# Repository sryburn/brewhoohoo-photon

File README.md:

A particle photon based HERMS brewery controller with 3D printed encousure.
WORK IN PROGRESS

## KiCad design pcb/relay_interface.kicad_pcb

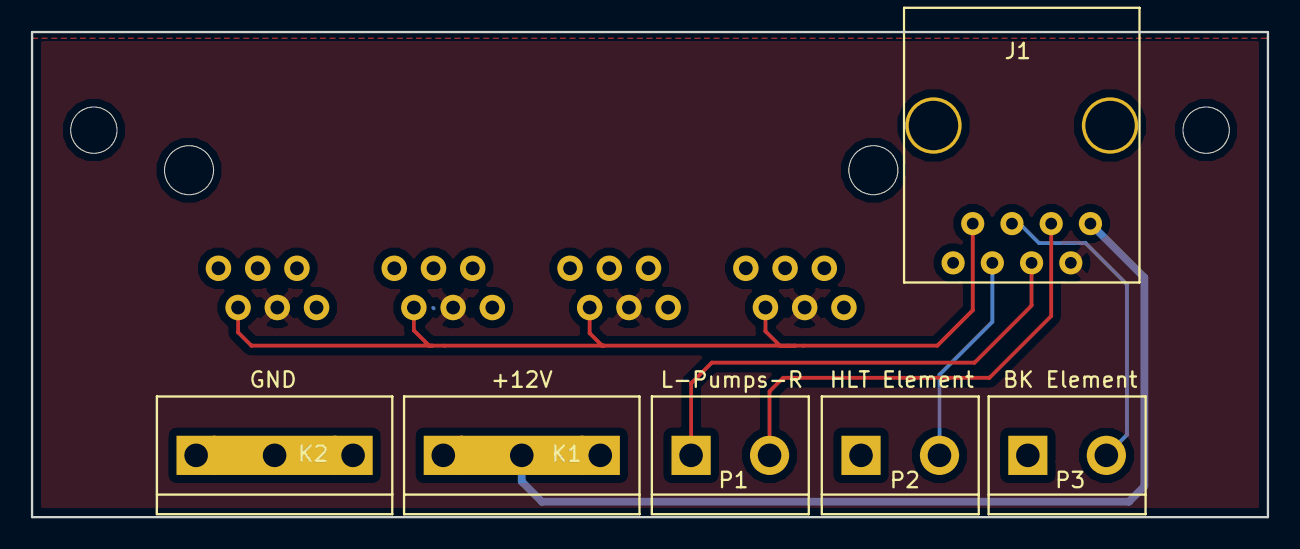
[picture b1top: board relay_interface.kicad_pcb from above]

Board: 2 copper layers, 80.0 x 31.4 mm, 7 parts (1 on the bottom side), 8 nets.

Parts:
J1: RJ45; RJ45_c-bmj-0102
J2: RJ12x4; CT660027-RJ12
K1, K2: CONN_3_V; bornier3
P1, P2, P3: CONN_2_V; bornier2

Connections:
+3V3: J1.2, J2.3, J2.9, J2.15, J2.21
+12V: J1.1, K1.1, K1.2, K1.3
/Element1: J1.6, P2.2
/Element2: J1.5, P3.2
/Pump1: J1.3, P1.2
/Pump2: J1.4, P1.1
/Temperature: J1.7, J2.5, J2.11, J2.17, J2.23
GND: J1.8, J2.4, J2.10, J2.16, J2.22, K2.1, K2.2, K2.3, P2.1, P3.1

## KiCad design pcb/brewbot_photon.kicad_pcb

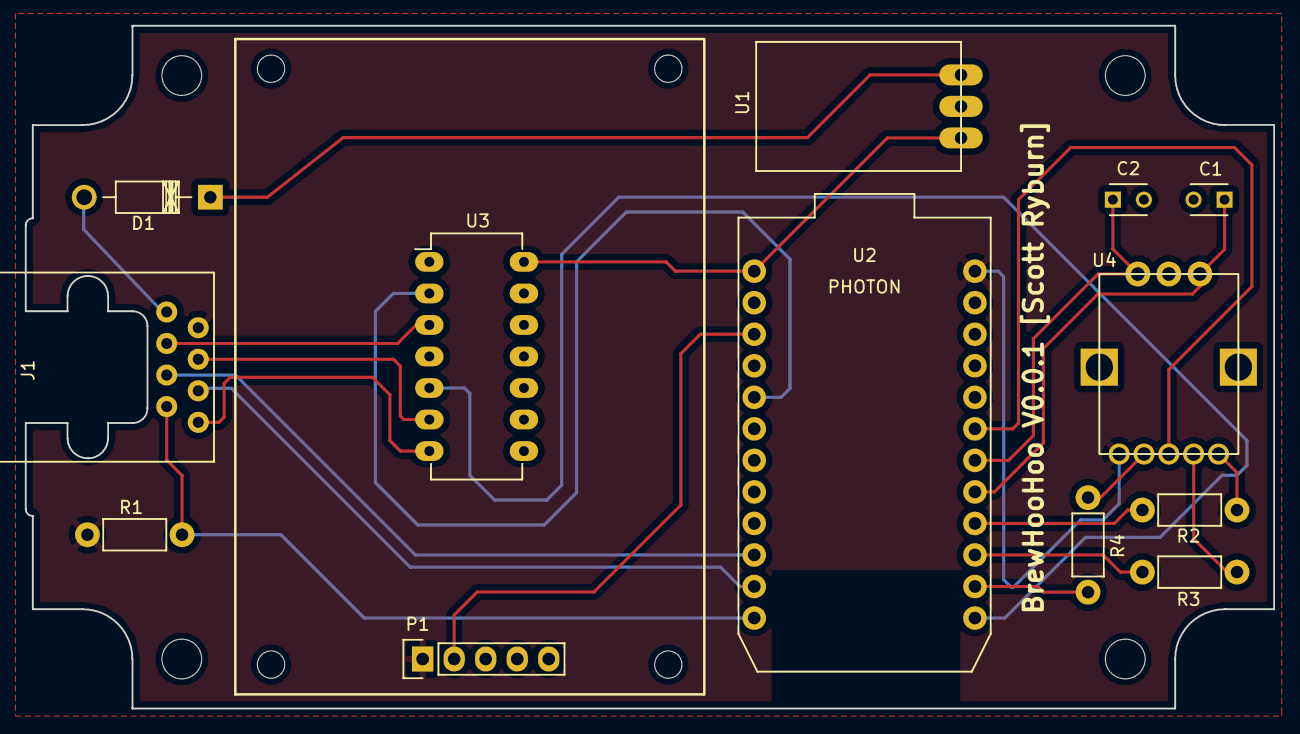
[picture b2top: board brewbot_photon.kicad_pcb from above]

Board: 2 copper layers, 100.6 x 55.0 mm, 17 parts (0 on the bottom side), 22 nets.

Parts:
C1, C2: 0.1uf; C_Disc_D3_P2.5
D1: 1N4007; Diode_DO-41_SOD81_Horizontal_RM10
J1: RJ45; RJ45_cA121601-ND_slim
P1: CONN_01X05; Pin_Header_Straight_1x05
R1: 4.7k; Resistor_Horizontal_RM7mm
R2: 56; Resistor_Horizontal_RM7mm
R3, R4: 1; Resistor_Horizontal_RM7mm
U1: 7805; OKI-78SR-5-1.5-W36H-C
U2: PHOTON; photon
U3: 74AHC125; DIP-14_W7.62mm_LongPads
U4: RGBEnc; RGB_Encoder
h1, h2, h3, h4: MountingHole_2.2mm_M2

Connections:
+3V3: J1.2, P1.1, R1.2, U2.24, U4.5
+5V: U1.VO, U2.1, U3.14
+12V: D1.2, J1.1
/Element1: J1.6, U2.11
/Element2: J1.5, U2.10
/Pump1: J1.3, U3.3
/Pump2: J1.4, U3.6
/Temperature: J1.7, R1.1, U2.12
GND: C1.2, C2.2, J1.8, P1.5, U1.GND, U2.2, U3.1, U3.4, U3.7, U4.7
unnamed: C1.1, U2.17, U4.6
unnamed: C2.1, U2.18, U4.8
unnamed: D1.1, U1.VI
unnamed: P1.2, U2.3
unnamed: R2.1, U4.1
unnamed: R2.2, U2.16
unnamed: R3.1, U4.2
unnamed: R3.2, U2.15
unnamed: R4.1, U4.4
unnamed: R4.2, U2.14
unnamed: U2.5, U3.2
unnamed: U2.13, U3.5
unnamed: U2.19, U4.3

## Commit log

2017-02-18 added PCBs
2017-02-18 Added enclosure
2017-02-18 Rename brewbot_control_interface.kicad_pcb to brewbot_relay_interface.kicad_pcb
2017-02-18 Rename brewbot_control_fp.kicad_pcb to front_panel.kicad_pcb
2017-02-18 Rename brewbot_relay_interface.kicad_pcb to relay_interface.kicad_pcb
2017-02-18 Rename brewbot_photon.kicad_pcb to photon_controller.kicad_pcb
2017-02-18 Rename brewbot-photon.ino to brewhoohoo.ino
2017-02-18 added schematics
2017-08-27 Add System thread
    -add support for system thread, network issues will no longer halt the loop
    -remove network connect/disconnect option
    -increased time between publish events to conform to publish webhook rate limit
2017-08-27 Brewday notes
2018-03-27 Add project properties file, Include libraries not available via particle cloud, restructure folders, update test probe addresses
2018-03-28 move OLED display rendering functions to separate class
2018-03-30 refactor display class
2018-04-01 More refactoring, remove a few unnecessesary globals
2018-11-26 just a test
2019-01-15 Implemented the ability to set a target mash temperature in place of an HLT setpoint with (very) basic control loop
2022-07-17 added absorbtion data
2024-10-28 Update Brew Steps.md
    added water profile for hazy
2024-10-28 Update Brew Steps.md
    update chlorine removal note
2024-10-28 Update Brew Steps.md
    formatting
